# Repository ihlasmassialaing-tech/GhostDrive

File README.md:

# GhostDrive — Hardware Security-Audit Device (BadUSB)

> A from-scratch embedded hardware project: a custom USB device (own PCB + firmware)
> designed for authorized security-awareness demonstrations. Built for a supervised
> engineering course.

**Author:** Ihlas Massiala — engineering student, IoT & Cybersecurity, Polytech Lille.
**Stack:** ATmega32U4 · AT45DB161E (external SPI flash) · KiCad (PCB) · C / LUFA (USB firmware) · Python

### ⚠️ Disclaimer — educational use only
This is an **academic project** built to learn embedded systems and hardware-security
concepts. It must only be used on hardware you **own** or have **explicit written
authorization** to test. The author takes no responsibility for any misuse.

### Overview (English)
GhostDrive is a small **USB device of the BadUSB family**. It presents itself to a host as a
standard USB mass-storage key (a 2 MB drive) while also acting as a USB keyboard (HID),
illustrating why untrusted USB peripherals are a real security risk. The behaviour is selected
**offline** with a mechanical DIP switch — no battery required.

The project was designed end to end:
- **Hardware:** a custom PCB in **KiCad** around an **ATmega32U4** MCU with an external
  **AT45DB161E** SPI flash, in a USB-key form factor (schematic, routing, production files).
- **Firmware:** written in **C** on top of the **LUFA** USB stack — USB composite-device
  enumeration, SPI communication with the flash (FAT12 geometry) and reading the hardware
  configuration switches.
- **Tooling:** a small **Python** generator and low-level test firmware (status-LED board bring-up).

### What this project demonstrates
Embedded C, USB device programming (LUFA), SPI/flash handling, PCB design (KiCad), hardware
bring-up and debugging, and a practical understanding of a well-known physical-access attack
class — the kind of hands-on background useful for offensive security / penetration testing.

> 🇫🇷 **Version française complète ci-dessous.**

---

# GhostDrive - Plateforme d'Audit de Sécurité Furtive & Autonome

## Description Générale
GhostDrive est un outil d'audit de sécurité matériel de type BadUSB. Il a été conçu pour exécuter des injections de commandes automatisées tout en se camouflant derrière l'apparence d'un périphérique USB de stockage standard (clé USB de 2 Mo). 

L'architecture matérielle repose sur un microcontrôleur ATmega32U4 couplé à une mémoire flash SPI externe (AT45DB161E). La sélection du vecteur d'attaque en mode "Hors-Ligne" est gérée par un DIP Switch mécanique, permettant de calibrer le dispositif sans nécessiter de batterie embarquée. Une fois branché, le périphérique est reconnu comme un périphérique USB Composite (Mass Storage + Clavier HID).

## Architecture du Dépôt

Le projet est divisé en trois dossiers principaux :

* **`Documentation/`** : Contient les fiches techniques (datasheets) des composants critiques utilisés pour la conception.
    * `atmega32U4_datasheet.pdf` : Microcontrôleur principal.
    * `AT45DB161E.pdf` : Puce mémoire Flash SPI (2 Mo) pour le stockage de masse.
    * `MAX1811.pdf` : Contrôleur de charge LiPo (intégré au schéma pour une alimentation hybride optionnelle).

* **`Hardware/`** : Contient les fichiers de conception électronique réalisés sous KiCad.
    * `ghost_drive.kicad_sch` : Schéma de principe.
    * `ghost_drive.kicad_pcb` : Routage de la carte mère au format clé USB.
    * `production/` : Fichiers de fabrication (Gerbers, BOM, Pick&Place).

* **`Logiciel/`** : Contient les différents firmwares développés (basés sur la bibliothèque LUFA).
    * `test_led/` : Programme de test unitaire bas niveau permettant de valider l'alimentation, le fonctionnement de l'horloge interne et les soudures de la carte via le clignotement d'une LED de statut.
    * `GhostDrive/` : Firmware principal complet gérant l'énumération USB Composite, la communication SPI avec la mémoire flash (géométrie FAT12), la lecture matérielle des DIP Switchs et l'exécution automatisée des payloads HID.

## Fonctionnalités Principales

1.  **Configuration Matérielle Hors-Ligne :** Sélection du payload via DIP Switch physique avant connexion.
2.  **Camouflage (Leurre) :** Montage automatique d'un volume de stockage FAT12 vierge et fonctionnel de 2 Mo pour lever les soupçons de l'utilisateur cible.
3.  **Exécution Furtive :** Frappe automatisée de séquences de touches programmées (clavier virtuel) en arrière-plan pendant la consultation du volume de stockage.

## Compilation et Flashage

Pour compiler et flasher les firmwares sur l'ATmega32U4, les outils suivants sont requis sous Linux : `avr-gcc`, `avr-libc`, `make` et `dfu-programmer`.

1.  Ouvrir un terminal dans le dossier du firmware souhaité (`Logiciel/GhostDrive/` ou `Logiciel/test_led/`).
2.  Passer la carte en mode Bootloader (Maintenir le bouton HWB, appuyer sur RESET, relâcher HWB).
3.  Lancer la compilation et le flashage :
    ```bash
    make clean
    make
    make dfu
    ```

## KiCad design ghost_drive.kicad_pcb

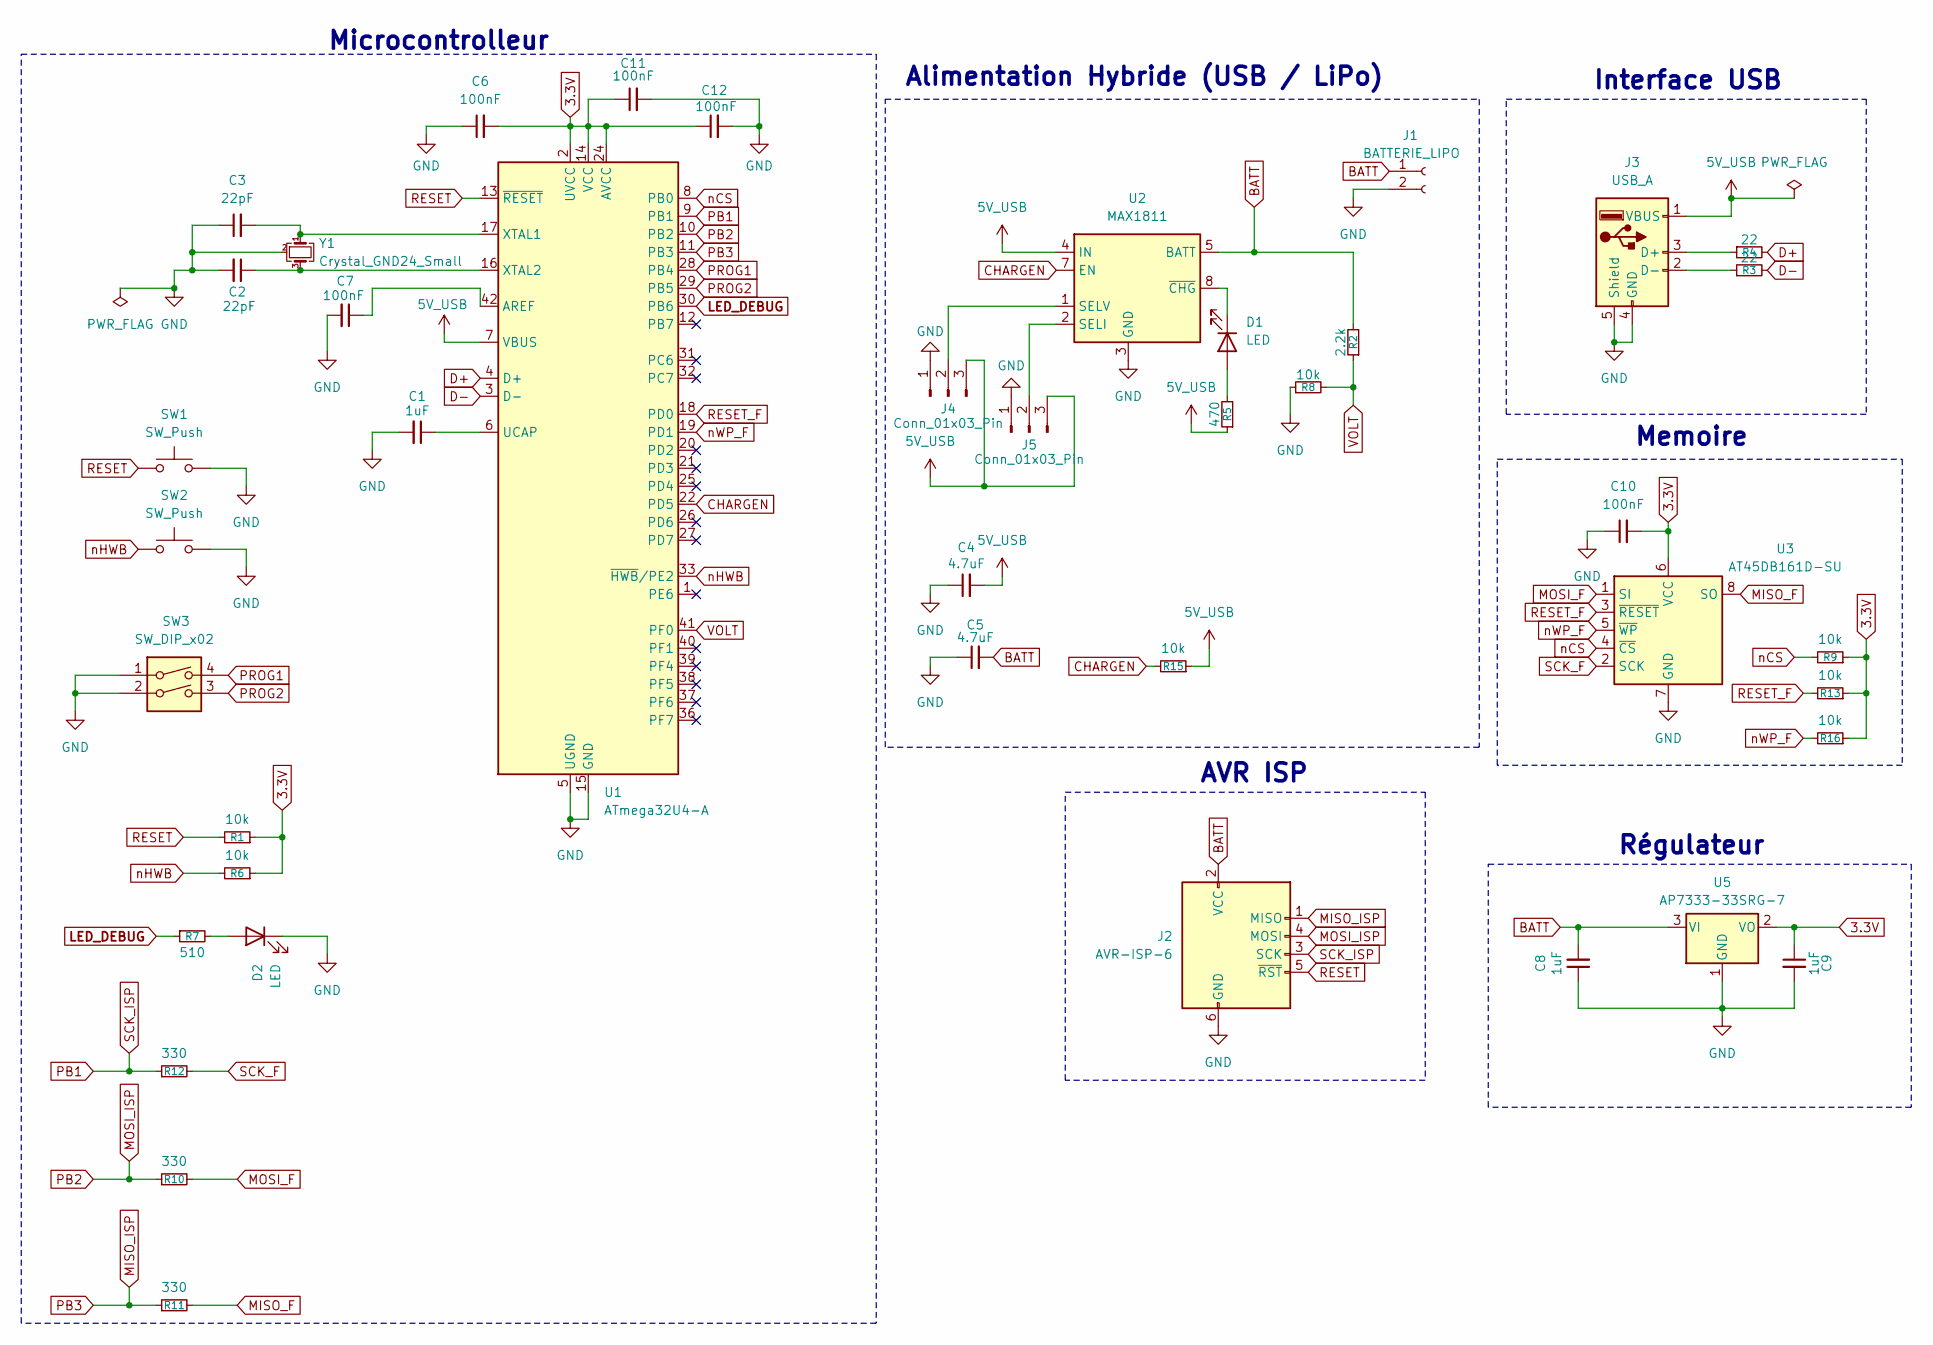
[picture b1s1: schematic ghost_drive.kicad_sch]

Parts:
C1, C8, C9: 1uF; C_0603_1608Metric_Pad1.08x0.95mm_HandSolder
C2, C3: 22pF; C_0603_1608Metric_Pad1.08x0.95mm_HandSolder
C4, C5: 4.7uF; C_0603_1608Metric_Pad1.08x0.95mm_HandSolder
C6, C7, C10, C11, C12: 100nF; C_0603_1608Metric_Pad1.08x0.95mm_HandSolder
D1, D2: LED; LED_0603_1608Metric_Pad1.05x0.95mm_HandSolder
J1: BATTERIE_LIPO; JST_PH_S2B-PH-K_1x02_P2.00mm_Horizontal
J2: AVR-ISP-6; PinHeader_2x03_P2.54mm_Vertical
J3: USB_A; USB_A_Molex_48037-2200_Horizontal
J4, J5: Conn_01x03_Pin; PinHeader_1x03_P2.54mm_Vertical
R1, R6, R8, R9, R13, R15, R16: 10k; R_0603_1608Metric_Pad0.98x0.95mm_HandSolder
R2: 2.2k; R_0603_1608Metric_Pad0.98x0.95mm_HandSolder
R3, R4: 22; R_0603_1608Metric_Pad0.98x0.95mm_HandSolder
R5: 470; R_0603_1608Metric_Pad0.98x0.95mm_HandSolder
R7: 510; R_0603_1608Metric_Pad0.98x0.95mm_HandSolder
R10, R11, R12: 330; R_0603_1608Metric_Pad0.98x0.95mm_HandSolder
SW1, SW2: SW_Push; SW_PUSH_6mm_H5mm
SW3: SW_DIP_x02; SW_DIP_SPSTx02_Piano_10.8x6.64mm_W7.62mm_P2.54mm
U1: ATmega32U4-A; TQFP-44_10x10mm_P0.8mm
U2: MAX1811; SOIC-8_3.9x4.9mm_P1.27mm
U3: AT45DB161D-SU; SOIC-8_5.3x5.3mm_P1.27mm
U5: AP7333-33SRG-7; SOT-223-3_TabPin2
Y1: Crystal_GND24_Small; Crystal_SMD_3225-4Pin_3.2x2.5mm

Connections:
3.3V: C6.2, C9.1, C10.2, C11.1, C12.1, R1.1, R6.1, R9.1, R13.1, R16.1, U1.2 (UVCC), U1.14 (VCC), U1.24 (AVCC), U1.34 (VCC), U1.44 (AVCC), U3.6 (VCC), U5.2 (VO)
5V_USB: C4.2, J3.1 (VBUS), J4.3, J5.3, R5.1, R15.1, U1.7 (VBUS), U2.4 (IN)
BATT: C5.2, C8.2, J1.1, J2.2 (VCC), R2.2, U2.5 (BATT), U5.3 (VI)
CHARGEN: R15.2, U1.22 (PD5), U2.7 (EN)
D+: R4.2, U1.4 (D+)
D-: R3.2, U1.3 (D-)
GND: C1.2, C2.2, C3.1, C4.1, C5.1, C6.1, C7.2, C8.1, C9.2, C10.1, C11.2, C12.2, D2.1 (K), J1.2, J2.6 (GND), J3.4 (GND), J3.5 (Shield), J4.1, J5.1, R8.1, SW1.2, SW2.2, SW3.1, SW3.2, U1.5 (UGND), U1.15 (GND), U1.23 (GND), U1.35 (GND), U1.43 (GND), U2.3 (GND), U2.6 (GND), U3.7 (GND), U5.1 (GND), Y1.2 (G), Y1.4 (G)
LED_DEBUG: R7.1, U1.30 (PB6)
MISO_F: R11.2, U3.8 (SO)
MISO_ISP: J2.1 (MISO), R11.1, U1.11 (PB3)
MOSI_F: R10.2, U3.1 (SI)
MOSI_ISP: J2.4 (MOSI), R10.1, U1.10 (PB2)
unnamed: D1.2 (A), R5.2
unnamed: D1.1 (K), U2.8 (~CHG)
unnamed: D2.2 (A), R7.2
unnamed: J3.3 (D+), R4.1
unnamed: J3.2 (D-), R3.1
unnamed: J4.2, U2.1 (SELV)
unnamed: J5.2, U2.2 (SELI)
unnamed: C7.1, U1.42 (AREF)
unnamed: C1.1, U1.6 (UCAP)
unnamed: C3.2, U1.17 (XTAL1), Y1.1
unnamed: C2.1, U1.16 (XTAL2), Y1.3
PB1: J2.3 (SCK), R12.1, U1.9 (PB1)
PROG1: SW3.4, U1.28 (PB4)
PROG2: SW3.3, U1.29 (PB5)
RESET: J2.5 (~RST), R1.2, SW1.1, U1.13 (~RESET)
RESET_F: R13.2, U1.18 (PD0), U3.3 (~RESET)
SCK_F: R12.2, U3.2 (SCK)
VOLT: R2.1, R8.2, U1.41 (PF0)
nCS: R9.2, U1.8 (PB0), U3.4 (~CS)
nHWB: R6.2, SW2.1, U1.33 (~HWB/PE2)
nWP_F: R16.2, U1.19 (PD1), U3.5 (~WP)

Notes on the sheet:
Régulateur
Memoire
AVR ISP
Interface USB
Alimentation Hybride (USB / LiPo)
Microcontrolleur

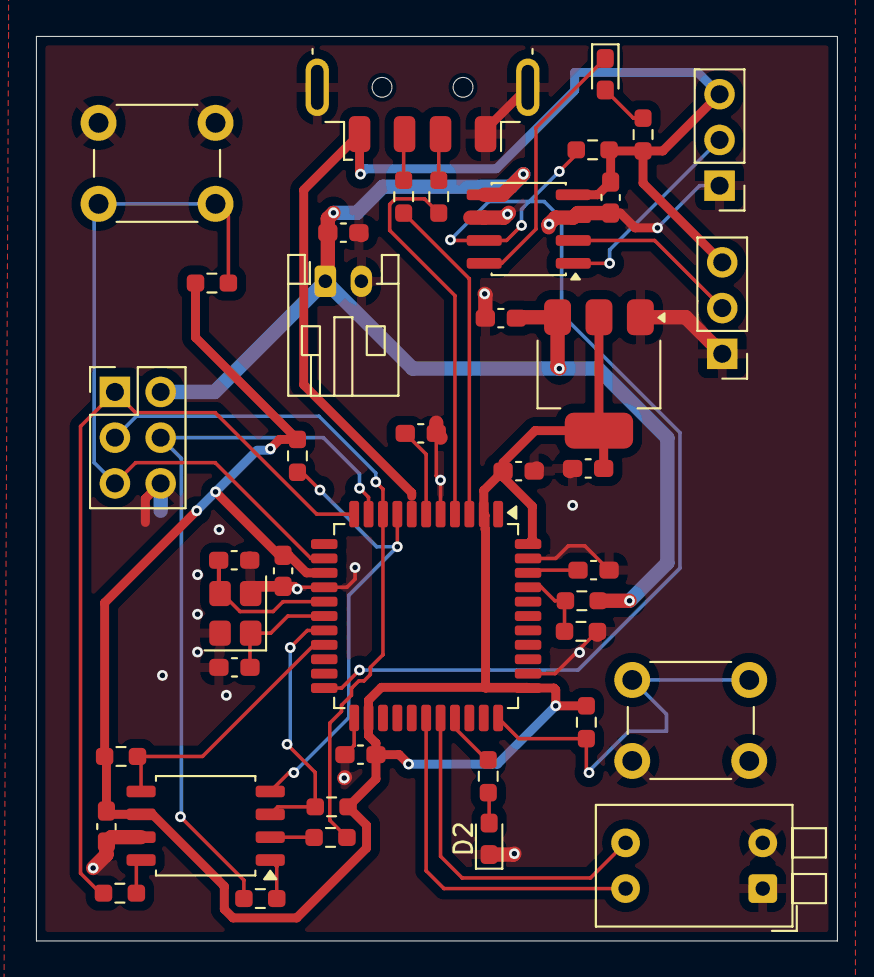
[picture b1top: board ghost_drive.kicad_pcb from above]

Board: 2 copper layers, 44.5 x 50.2 mm, 42 parts (0 on the bottom side), 33 nets.

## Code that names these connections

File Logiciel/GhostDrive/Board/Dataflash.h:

#ifndef __BOARD_DATAFLASH_H__
#define __BOARD_DATAFLASH_H__

#include <avr/io.h>

#define DATAFLASH_TOTALCHIPS   1
#define DATAFLASH_NO_CHIP      0
#define DATAFLASH_CHIP1        (1 << 0) // PB0
#define DATAFLASH_PAGE_SIZE    512 
#define DATAFLASH_PAGES        4096

/* Commandes standards Atmel Dataflash */
#define DF_CMD_GETSTATUS                         0xD7
#define DF_CMD_MAINMEMTOBUFF1                    0x53
#define DF_CMD_MAINMEMTOBUFF2                    0x55
#define DF_CMD_BUFF1READ                         0xD4
#define DF_CMD_BUFF2READ                         0xD6
#define DF_CMD_BUFF1WRITE                        0x84
#define DF_CMD_BUFF2WRITE                        0x87
#define DF_CMD_BUFF1TOMAINMEMWITHERASE           0x83
#define DF_CMD_BUFF2TOMAINMEMWITHERASE           0x86
#define DF_CMD_MAINMEMPAGEREAD                   0xD2
#define DF_CMD_MAINMEMPAGEPROGTHROUGHBUFF1       0x82
#define DF_CMD_MAINMEMPAGEPROGTHROUGHBUFF2       0x85
#define DF_CMD_PAGEERASE                         0x81
#define DF_CMD_BLOCKERASE                        0x50
#define DF_CMD_READMANUFACTURERDEVICEINFO        0x9F

#define DF_MANUFACTURER_ATMEL                    0x1F
#define DF_STATUS_SECTORPROTECTION_ON            (1 << 1)

static const uint8_t DF_CMD_SECTORPROTECTIONOFF[4] = {0x3D, 0x2A, 0x7F, 0x9A};

/* 1. Initialisation manuelle pure (sans LUFA) */
static inline void Dataflash_Init(void)
{
    // PB0 (CS), PB1 (SCK), PB2 (MOSI) en sortie
    DDRB |= (1 << PB0) | (1 << PB1) | (1 << PB2);
    // PB3 (MISO) en entrée
    DDRB &= ~(1 << PB3);
    
    // CS à l'état HAUT (inactif) et Pull-up sur MISO
    PORTB |= (1 << PB0) | (1 << PB3);

    // Configuration SPI pure : Master, Mode 0, Vitesse très lente (F_CPU/16)
    SPCR = (1 << SPE) | (1 << MSTR) | (1 << SPR0);
    SPSR = 0;
}

/* 2. Transfert SPI manuel */
static inline uint8_t Dataflash_TransferByte(const uint8_t Byte)
{
    SPDR = Byte;
    while (!(SPSR & (1 << SPIF))); // Attend la fin de l'envoi
    return SPDR;
}

static inline void Dataflash_SendByte(const uint8_t Byte) {
    Dataflash_TransferByte(Byte);
}

static inline uint8_t Dataflash_ReceiveByte(void) {
    return Dataflash_TransferByte(0x00); // Horloge artificielle pour lire
}

/* 3. Gestion du Chip Select */
static inline uint8_t Dataflash_GetSelectedChip(void) {
    return (!(PINB & DATAFLASH_CHIP1)) ? DATAFLASH_CHIP1 : DATAFLASH_NO_CHIP;
}

static inline void Dataflash_SelectChip(const uint8_t ChipMask) {
    PORTB &= ~ChipMask; 
}

static inline void Dataflash_DeselectChip(void) {
    PORTB |= DATAFLASH_CHIP1; 
}

static inline void Dataflash_SelectChipFromPage(const uint16_t PageAddress) {
    Dataflash_DeselectChip();
    Dataflash_SelectChip(DATAFLASH_CHIP1);
}

static inline void Dataflash_ToggleSelectedChipCS(void) {
    Dataflash_DeselectChip();
    Dataflash_SelectChip(DATAFLASH_CHIP1);
}

/* 4. Sécurité anti-plantage avec Timeout */
static inline void Dataflash_WaitWhileBusy(void)
{
    Dataflash_ToggleSelectedChipCS();
    Dataflash_SendByte(0xD7); 
    uint16_t timeout = 50000;
    while (!(Dataflash_ReceiveByte() & (1 << 7)) && timeout > 0) {
        timeout--;
    }
    Dataflash_ToggleSelectedChipCS();
}

static inline void Dataflash_SendAddressBytes(uint16_t PageAddress, const uint16_t BufferByte)
{
    Dataflash_SendByte((PageAddress >> 6));
    Dataflash_SendByte((PageAddress << 2) | (BufferByte >> 8));
    Dataflash_SendByte(BufferByte);
}

#endif

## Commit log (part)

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2026-03-10 Téléverser les fichiers vers "/"
2026-03-10 Supprimer 2025-PSE-14-systeme.zip
2026-03-10 Quelques modifications
2026-03-13 Quelques corrections
2026-03-17 Des modifications schématique
2026-03-17 quelque changement
2026-04-06 routage fini
2026-04-07 Passer l'alim en 0.5 mm
2026-04-07 programation
2026-04-07 changement taille alim en 0,5 mm
2026-04-07 Téléverser les fichiers vers "Hardware"
2026-04-07 deplacer vers dossier hardware
2026-04-08 PCB en production
2026-05-26 ajout des 4 script
2026-05-27 la clé peut mtn stocker des ficher et en restituer le contenu.
2026-05-31 Téléverser les fichiers vers "Documentation"
2026-05-31 rename
2026-05-31 supression dossier doublon
2026-05-31 readme
